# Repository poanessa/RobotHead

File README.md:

# RobotHead

Welcome to the PSU Robotics Department's robot head repository.<p>
Here you will find all files related to the production of the robot head created in in the 2016-2017 school term.<p>
This project was created by Tuna Poanessa (hardware) and Daniel Diaz (software).<p>
Have questions?  Please feel free to email me at poanessa@gmail.com

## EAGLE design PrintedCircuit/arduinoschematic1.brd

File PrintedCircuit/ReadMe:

This folder contains the start of a printed circuit board to control the head that is arduino based.  
The schematic is complete but the breadboard layout needs work!

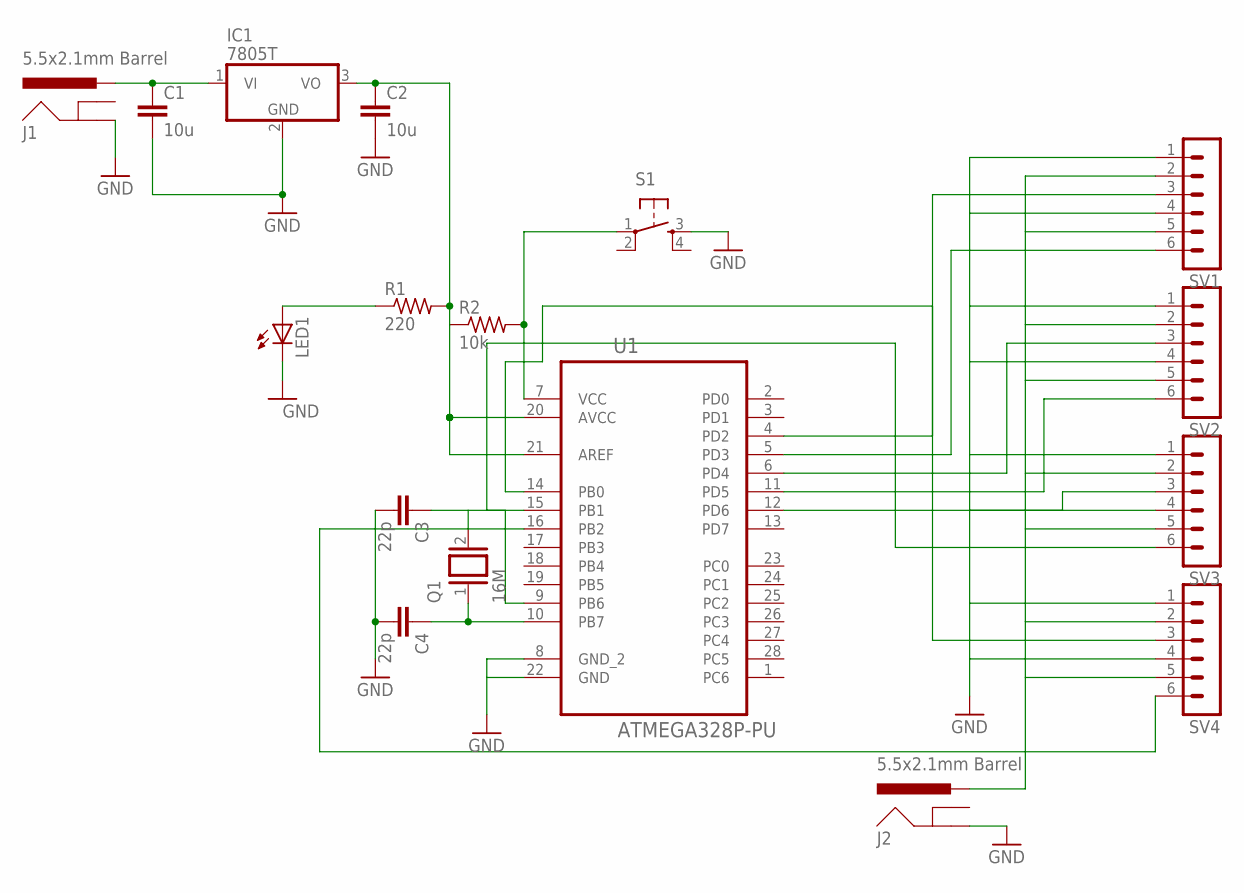
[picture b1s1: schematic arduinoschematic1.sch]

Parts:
C1, C2: 10u; C050-030X075
C3, C4: 22p; C025-030X050
IC1: 7805T; TO220H
J1, J2: 5.5x2.1mm Barrel; POWER_JACK_SMD
LED1: LEDSQR2X5; LED2X5
Q1: 16M; QS
R1: 220; 0204/5
R2: 10k; 0204/5
S1: TAC_SWITCHSMD; TACTILE-PTH
SV1, SV2, SV3, SV4: MA06-1
U1: ATMEGA328P-PU; DIP254P762X457-28

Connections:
GND: C1.2, C2.2, C3.2, C4.2, IC1.2 (GND), J1.P$4 (GND), J2.P$4 (GND), LED1.K (C), S1.3, SV1.1, SV1.4, SV2.1, SV2.4, SV3.1, SV3.4, SV4.1, SV4.4, U1.8 (GND_2), U1.22 (GND)
unnamed: C2.1, IC1.3 (VO), R1.2, R2.1, U1.20 (AVCC), U1.21 (AREF)
unnamed: R2.2, S1.1, U1.7 (VCC)
unnamed: LED1.A, R1.1
unnamed: C4.1, Q1.1, U1.10 (PB7)
unnamed: SV1.3, U1.4 (PD2)
unnamed: C1.1, IC1.1 (VI), J1.VIN0 (PWR)
unnamed: C3.1, Q1.2, U1.9 (PB6)
unnamed: SV1.6, U1.5 (PD3)
unnamed: SV2.3, U1.6 (PD4)
unnamed: SV2.6, U1.11 (PD5)
unnamed: SV3.3, U1.12 (PD6)
unnamed: SV3.6, U1.14 (PB0)
unnamed: SV4.3, U1.15 (PB1)
unnamed: SV4.6, U1.16 (PB2)
unnamed: J2.VIN0 (PWR), SV1.2, SV1.5, SV2.2, SV2.5, SV3.2, SV3.5, SV4.2, SV4.5

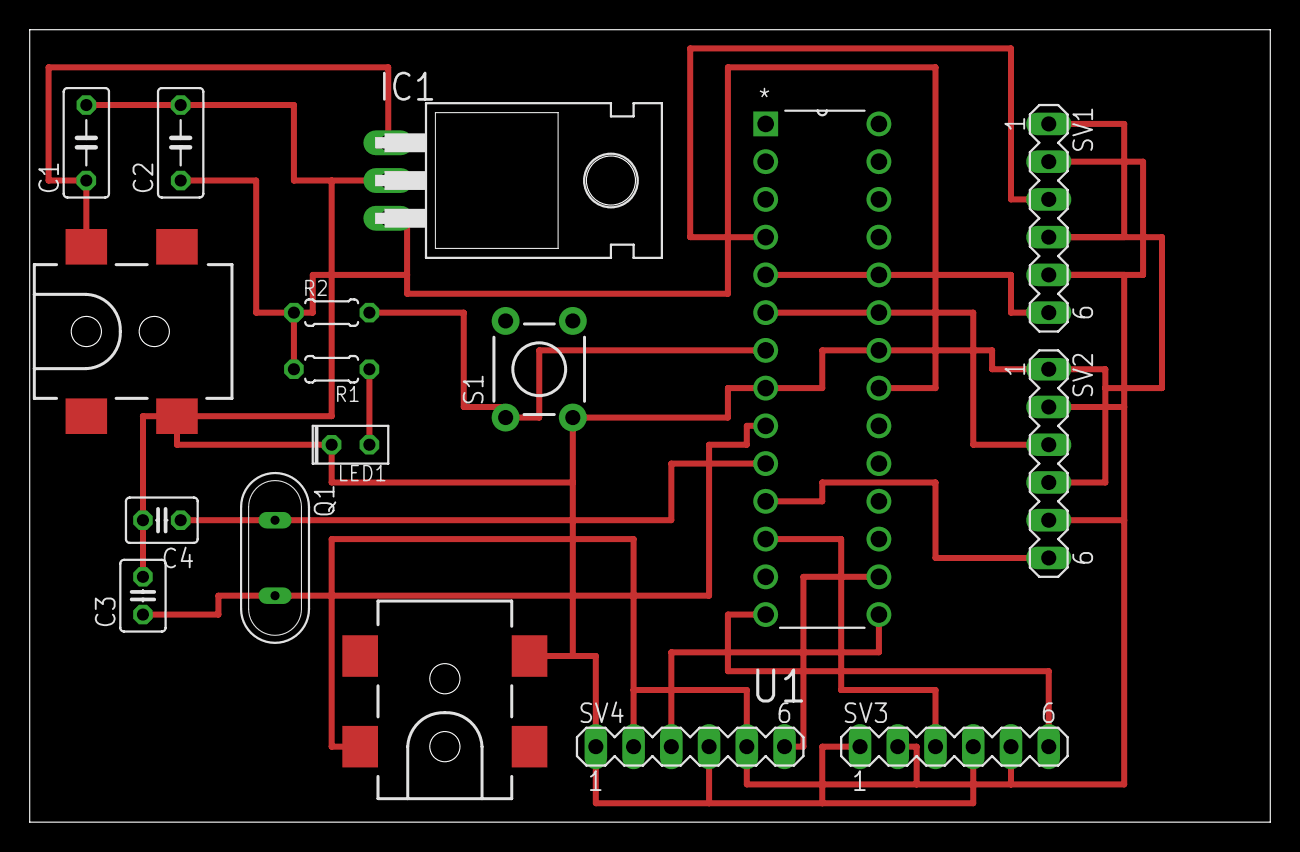
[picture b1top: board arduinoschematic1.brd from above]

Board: 2 copper layers, 83.5 x 53.3 mm, 17 parts (0 on the bottom side), 16 nets.

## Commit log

2017-05-31 genetic algorithm for eyelid control
    This code causes the eyes to blink when bright light is shined at a photoresistor
2017-05-31 Eyelid, eyes, and lips demo
    This code runs through a sequence of facial expressions using the eye, eyelid, and mouth mechanisms.
2017-05-31 Speaking code
    This program creates different mouth movements to replicate human speech.
    This code demos the use of the mouth movement functions by having the robot say "Hello, my name is Copernicus"
2017-05-31 Create media

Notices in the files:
parts and their libraries:
SparkFun-Connectors: Licensing: Creative Commons ShareAlike 4.0 International - https://creativecommons.org/licenses/by-sa/4.0
